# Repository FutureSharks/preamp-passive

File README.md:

# Preamp - Passive

This is the Arduino code, PCB layouts and 3D drawings for a HiFi passive preamplifier. It has the following features:

  * Volume control and input selection via encoder and Apple remote.
  * Uses a 256 step R2R relayed based attenuator.
  * Completely passive.
  * Only 5V power required.
  * [Adafruit NeoPixel](http://www.adafruit.com/category/168) shows volume level with colour.
  * Sleep mode with low power consumption: 0.9W.

Full build details can be found here:
http://www.diyaudio.com/forums/analog-line-level/275446-passive-preamp-arduino-based-remote-control-relay-r2r-input-selection.html

## Hardware

  * [MCP23S17](http://www.microchip.com/wwwproducts/Devices.aspx?product=MCP23S17): Controlled via SPI. This is the R2R relayed attenuator and controls the volume.
  * [MCP23S08](http://www.microchip.com/wwwproducts/Devices.aspx?product=MCP23S08): Controlled via SPI. For the input selector and mute.
  * [Adafruit NeoPixel](http://www.adafruit.com/category/168): Controlled via a single-wire control protocol.
  * IR sensor: Standard 38Khz type.
  * [Bourns EM14](https://www.bourns.com/pdfs/em14.pdf) Rotary Optical Encoder with switch.
  * [Modushop Galaxy Maggiorato GX187](http://www.modu.it/galaxyeng.html) with custom machined front and rear.

PCB and schematics are provided in EAGLE PCB format.

Front and rear panel 3D drawings are in AutoCAD format.

The IRremote library is from here:
https://github.com/z3t0/Arduino-IRremote

Adafruit NeoPixel library is from here:
https://github.com/adafruit/Adafruit_NeoPixel

## Photos

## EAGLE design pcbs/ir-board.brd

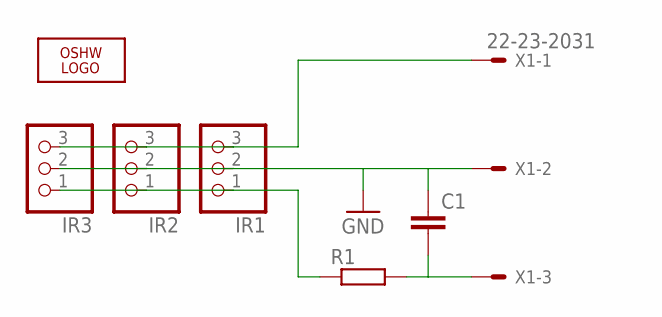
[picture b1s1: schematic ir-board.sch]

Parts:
C1: C-EUC1206; C1206
IR1, IR2, IR3: PINHD-1X3; 1X03
LOGO1: OSHW_LOGO_6MILX0200-NT; OSHW_6X200_NOTEXT
R1: R-EU_R1206; R1206
X1: 22-23-2031

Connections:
GND: C1.1, IR1.2, IR2.2, IR3.2, X1.2
unnamed: C1.2, R1.2, X1.3
OUT: IR1.3, IR2.3, IR3.3, X1.1
VS: IR1.1, IR2.1, IR3.1, R1.1

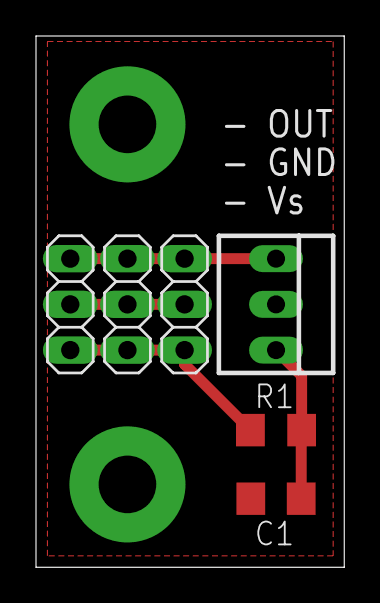
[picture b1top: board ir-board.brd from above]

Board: 2 copper layers, 17.1 x 29.5 mm, 7 parts (1 on the bottom side), 4 nets.

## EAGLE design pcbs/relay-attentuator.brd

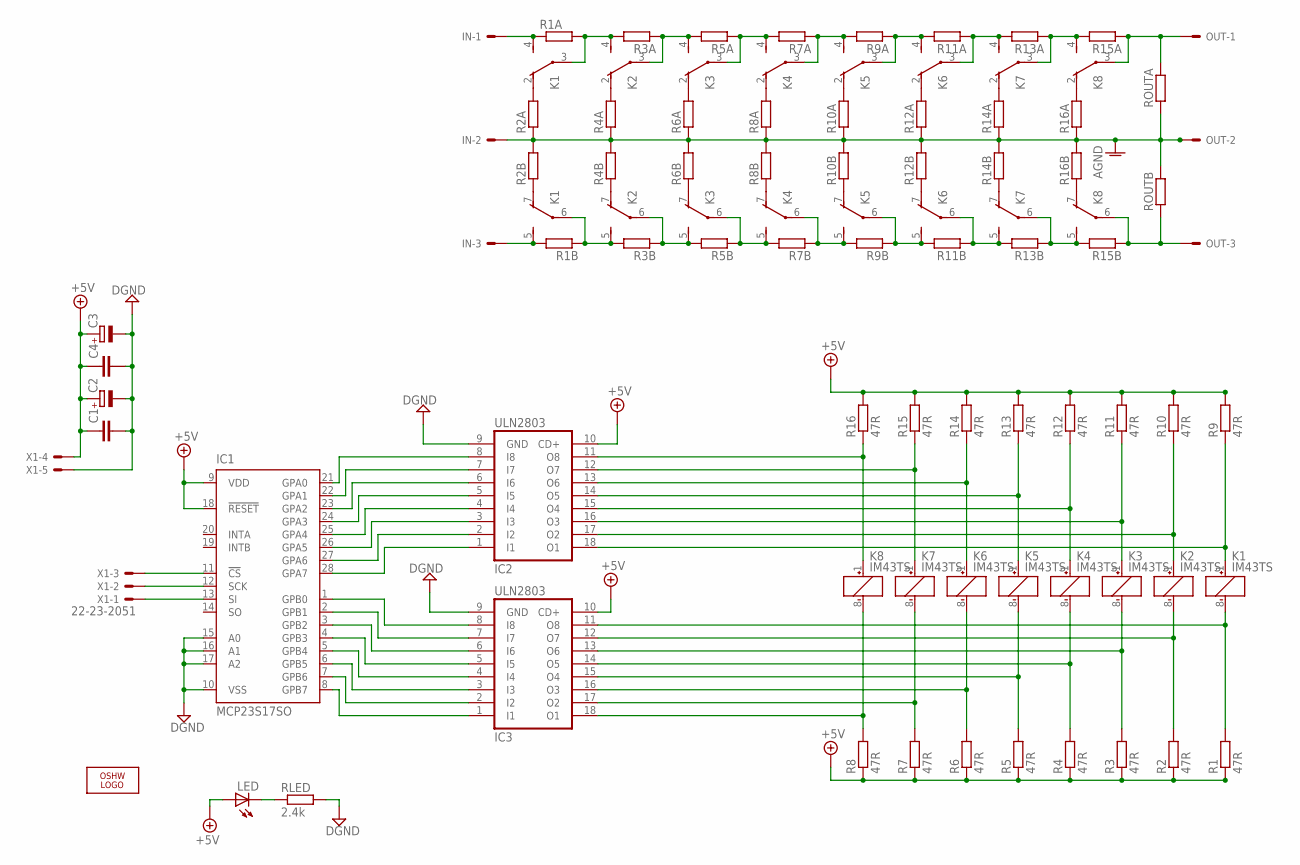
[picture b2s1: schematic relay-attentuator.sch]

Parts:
C1, C4: C-EUC1206; C1206
C2, C3: CPOL-EUE3.5-8; E3,5-8
IC1: MCP23S17SO; SO28W
IC2, IC3: ULN2803; SO-18W
IN: 22-23-2031
K1, K2, K3, K4, K5, K6, K7, K8: IM43TS
LED: LEDCHIPLED_1206; CHIPLED_1206
LOGO1: OSHW_LOGO_FILLX0200-NT; OSHW_FILLX200_NOTEXT
OUT: 22-23-2031
R1, R2, R3, R4, R5, R6, R7, R8, R9, R10, R11, R12, R13, R14, R15, R16: 47R; R1206
R1A, R1B, R2A, R2B, R3A, R3B, R4A, R4B, R5A, R5B, R6A, R6B, R7A, R7B, R8A, R8B, R9A, R9B, R10A, R10B, R11A, R11B, R12A, R12B, R13A, R13B, R14A, R14B, R15A, R15B, R16A, R16B: R-EU_R1206; R1206
RLED: 2.4k; R1206
ROUTA: R-EU_R1206; R1206
ROUTB: R-EU_R1206; R1206
X1: 22-23-2051

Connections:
+5V: C1.1, C2.+, C3.+, C4.1, IC1.9 (VDD), IC1.18 (!RESET), IC2.10 (CD+), IC3.10 (CD+), LED.A, R1.1, R2.1, R3.1, R4.1, R5.1, R6.1, R7.1, R8.1, R9.2, R10.2, R11.2, R12.2, R13.2, R14.2, R15.2, R16.2, X1.4
AGND: IN.2, OUT.2, R2A.1, R2B.2, R4A.1, R4B.2, R6A.1, R6B.2, R8A.1, R8B.2, R10A.1, R10B.2, R12A.1, R12B.2, R14A.1, R14B.2, R16A.1, R16B.2, ROUTA.1, ROUTB.2
ATT_INL: IN.1, K1.4 (S), R1A.1
ATT_INR: IN.3, K1.5 (S), R1B.2
CS: IC1.11 (!CS), X1.3
DGND: C1.2, C2.-, C3.-, C4.2, IC1.10 (VSS), IC1.15 (A0), IC1.16 (A1), IC1.17 (A2), IC2.9 (GND), IC3.9 (GND), RLED.2, X1.5
unnamed: IC2.11 (O8), K8.1 (+), R16.1
unnamed: IC3.11 (O8), K1.8 (-), R1.2
unnamed: IC3.17 (O2), K7.8 (-), R7.2
unnamed: IC3.13 (O6), K3.8 (-), R3.2
unnamed: IC3.14 (O5), K4.8 (-), R4.2
unnamed: K2.7 (O), R4B.1
unnamed: K1.7 (O), R2B.1
unnamed: K1.2 (O), R2A.2
unnamed: IC3.18 (O1), K8.8 (-), R8.2
unnamed: IC2.12 (O7), K7.1 (+), R15.1
unnamed: IC2.13 (O6), K6.1 (+), R14.1
unnamed: IC2.14 (O5), K5.1 (+), R13.1
unnamed: IC2.15 (O4), K4.1 (+), R12.1
unnamed: IC2.16 (O3), K3.1 (+), R11.1
unnamed: IC2.17 (O2), K2.1 (+), R10.1
unnamed: IC2.18 (O1), K1.1 (+), R9.1
unnamed: K3.7 (O), R6B.1
unnamed: IC3.12 (O7), K2.8 (-), R2.2
unnamed: IC3.16 (O3), K6.8 (-), R6.2
unnamed: IC3.15 (O4), K5.8 (-), R5.2
unnamed: K4.7 (O), R8B.1
unnamed: K5.7 (O), R10B.1
unnamed: K6.7 (O), R12B.1
unnamed: K7.7 (O), R14B.1
unnamed: K8.7 (O), R16B.1
unnamed: K2.2 (O), R4A.2
unnamed: K3.2 (O), R6A.2
unnamed: K4.2 (O), R8A.2
unnamed: K5.2 (O), R10A.2
unnamed: K6.2 (O), R12A.2
unnamed: K7.2 (O), R14A.2
unnamed: K8.2 (O), R16A.2
unnamed: IC1.28 (GPA7), IC2.1 (I1)
unnamed: IC1.27 (GPA6), IC2.2 (I2)
unnamed: IC1.26 (GPA5), IC2.3 (I3)
unnamed: IC1.25 (GPA4), IC2.4 (I4)
unnamed: IC1.24 (GPA3), IC2.5 (I5)
unnamed: IC1.23 (GPA2), IC2.6 (I6)
unnamed: IC1.22 (GPA1), IC2.7 (I7)
unnamed: IC1.21 (GPA0), IC2.8 (I8)
unnamed: IC1.8 (GPB7), IC3.1 (I1)
unnamed: IC1.7 (GPB6), IC3.2 (I2)
unnamed: IC1.6 (GPB5), IC3.3 (I3)
unnamed: IC1.5 (GPB4), IC3.4 (I4)
unnamed: IC1.4 (GPB3), IC3.5 (I5)
unnamed: IC1.3 (GPB2), IC3.6 (I6)
unnamed: IC1.2 (GPB1), IC3.7 (I7)
unnamed: IC1.1 (GPB0), IC3.8 (I8)
unnamed: K7.6, K8.5 (S), R13B.1, R15B.2
unnamed: K7.3, K8.4 (S), R13A.1, R15A.2
unnamed: K6.6, K7.5 (S), R11B.1, R13B.2
unnamed: LED.C, RLED.1
unnamed: K8.6, OUT.3, R15B.1, ROUTB.1
unnamed: K8.3, OUT.1, R15A.1, ROUTA.2
unnamed: K1.3, K2.4 (S), R1A.2, R3A.2
unnamed: K2.3, K3.4 (S), R3A.1, R5A.2
unnamed: K1.6, K2.5 (S), R1B.1, R3B.2
unnamed: K3.3, K4.4 (S), R5A.1, R7A.2
unnamed: K4.3, K5.4 (S), R7A.1, R9A.2
unnamed: K5.3, K6.4 (S), R9A.1, R11A.2
unnamed: K6.3, K7.4 (S), R11A.1, R13A.2
unnamed: K2.6, K3.5 (S), R3B.1, R5B.2
unnamed: K3.6, K4.5 (S), R5B.1, R7B.2
unnamed: K4.6, K5.5 (S), R7B.1, R9B.2
unnamed: K5.6, K6.5 (S), R9B.1, R11B.2
SCK: IC1.12 (SCK), X1.2
SI: IC1.13 (SI), X1.1

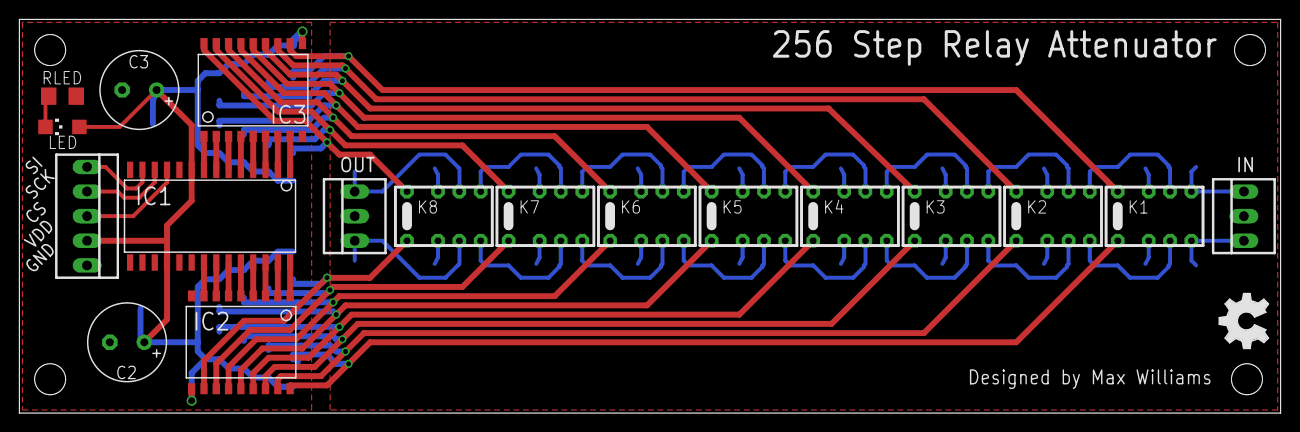
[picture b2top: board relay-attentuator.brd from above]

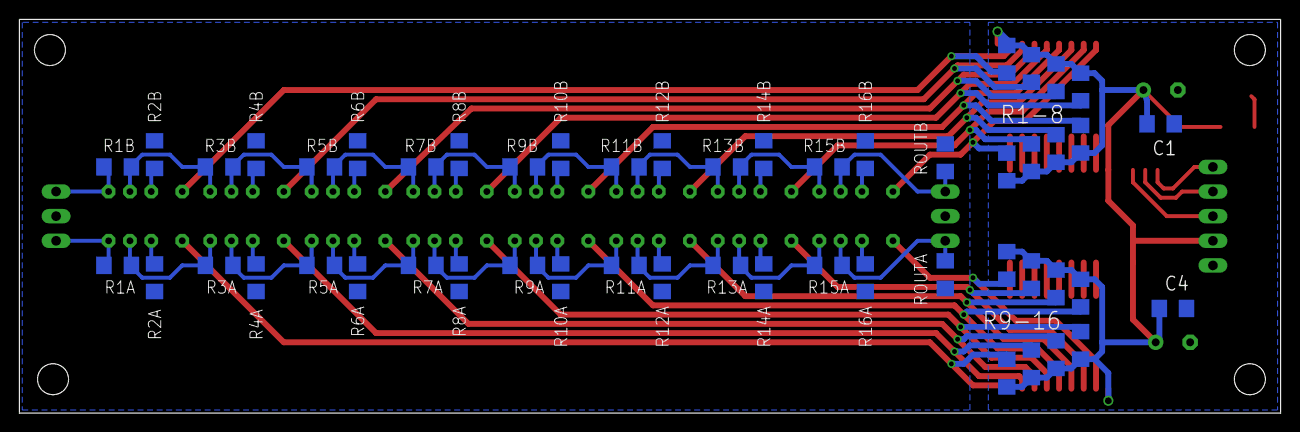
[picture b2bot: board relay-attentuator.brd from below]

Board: 2 copper layers, 130.2 x 40.6 mm, 71 parts (52 on the bottom side), 73 nets.

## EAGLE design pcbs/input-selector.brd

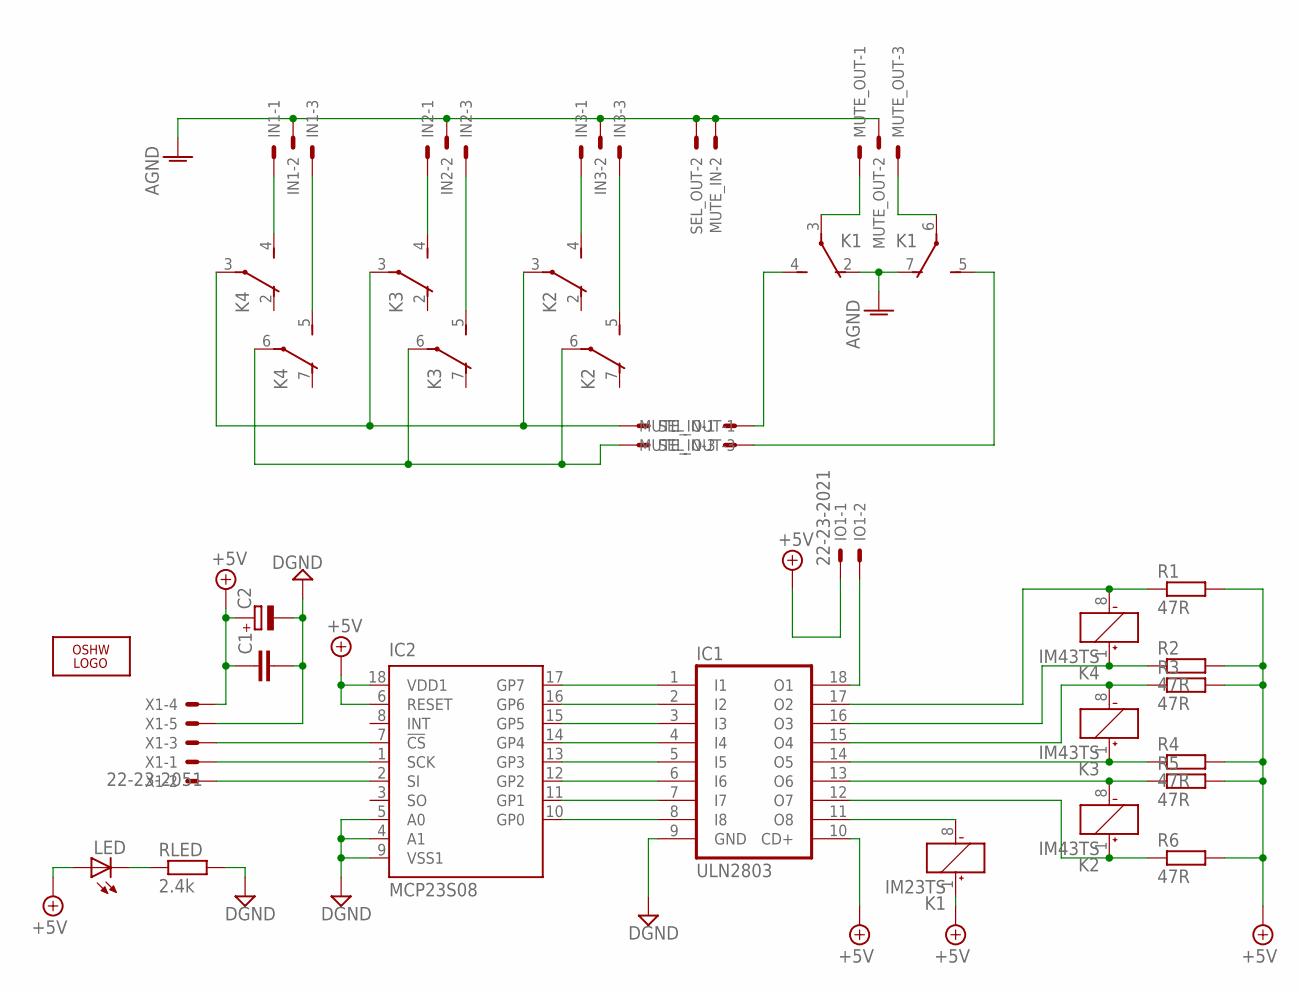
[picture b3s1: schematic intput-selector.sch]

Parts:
C1: C-EUC1206; C1206
C2: CPOL-EUC; PANASONIC_C
IC1: ULN2803; SO-18W
IC2: MCP23S08; SO-18W
IN1, IN2, IN3: 22-23-2031
IO1: 22-23-2021
K1: IM23TS; IM43TS
K2, K3, K4: IM43TS
LED: LEDCHIPLED_1206; CHIPLED_1206
LOGO1: OSHW_LOGO_FILLX0200-NT; OSHW_FILLX200_NOTEXT
MUTE_IN: 22-23-2031
MUTE_OUT: 22-23-2031
R1, R2, R3, R4, R5, R6: 47R; R1206
RLED: 2.4k; R1206
SEL_OUT: 22-23-2031
X1: 22-23-2051

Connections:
+5V: C1.1, C2.+, IC1.10 (CD+), IC2.6 (RESET), IC2.18 (VDD1), IO1.1, K1.1 (+), LED.A, R1.2, R2.2, R3.2, R4.2, R5.2, R6.2, X1.4
AGND: IN1.2, IN2.2, IN3.2, K1.2 (O), K1.7 (O), MUTE_IN.2, MUTE_OUT.2, SEL_OUT.2
CS: IC2.7 (!CS), X1.3
DGND: C1.2, C2.-, IC1.9 (GND), IC2.4 (A1), IC2.5 (A0), IC2.9 (VSS1), RLED.2, X1.5
INL: K2.3, K3.3, K4.3, SEL_OUT.1
INR: K2.6, K3.6, K4.6, SEL_OUT.3
unnamed: IC1.1 (I1), IC2.17 (GP7)
unnamed: IC1.2 (I2), IC2.16 (GP6)
unnamed: IC1.3 (I3), IC2.15 (GP5)
unnamed: IC1.5 (I5), IC2.13 (GP3)
unnamed: IC1.6 (I6), IC2.12 (GP2)
unnamed: IC1.7 (I7), IC2.11 (GP1)
unnamed: IC1.4 (I4), IC2.14 (GP4)
unnamed: IC1.8 (I8), IC2.10 (GP0)
unnamed: IC1.16 (O3), K4.1 (+), R2.1
unnamed: IC1.14 (O5), K3.1 (+), R4.1
unnamed: IC1.13 (O6), K2.8 (-), R5.1
unnamed: IC1.12 (O7), K2.1 (+), R6.1
unnamed: IC1.15 (O4), K3.8 (-), R3.1
unnamed: IC1.11 (O8), K1.8 (-)
unnamed: IC1.17 (O2), K4.8 (-), R1.1
unnamed: IC1.18 (O1), IO1.2
unnamed: K1.6, MUTE_OUT.3
unnamed: K1.3, MUTE_OUT.1
unnamed: IN1.1, K4.4 (S)
unnamed: IN1.3, K4.5 (S)
unnamed: IN2.1, K3.4 (S)
unnamed: IN2.3, K3.5 (S)
unnamed: IN3.1, K2.4 (S)
unnamed: IN3.3, K2.5 (S)
unnamed: LED.C, RLED.1
OUTL: K1.4 (S), MUTE_IN.1
OUTR: K1.5 (S), MUTE_IN.3
SCK: IC2.1 (SCK), X1.1
SI: IC2.2 (SI), X1.2

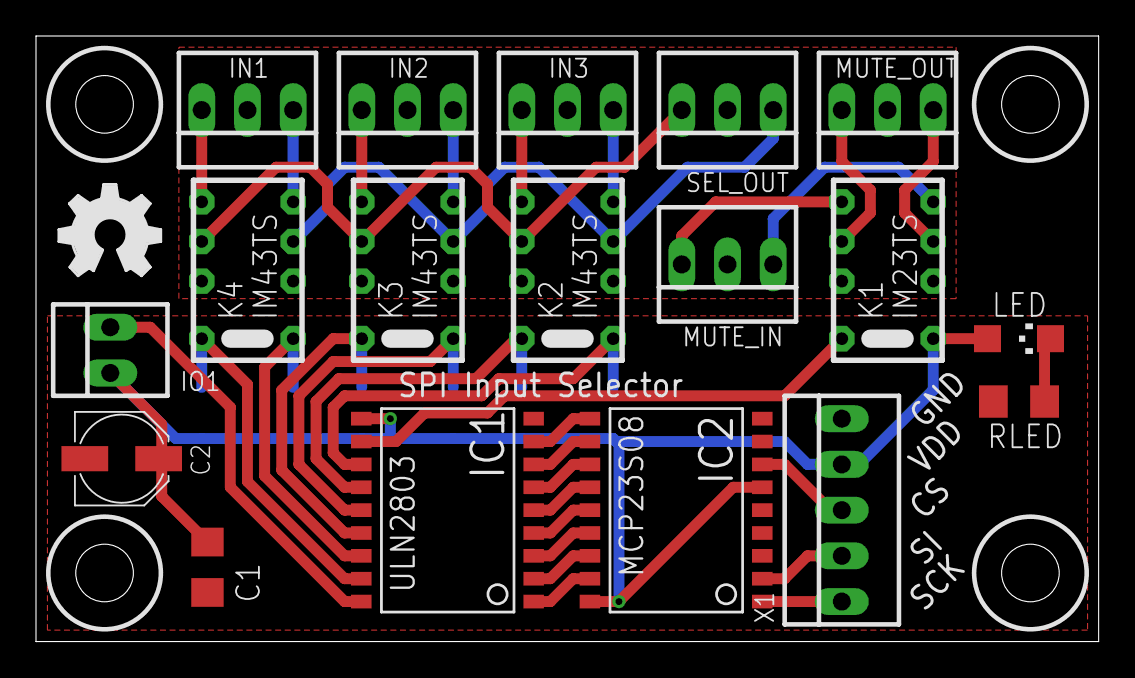
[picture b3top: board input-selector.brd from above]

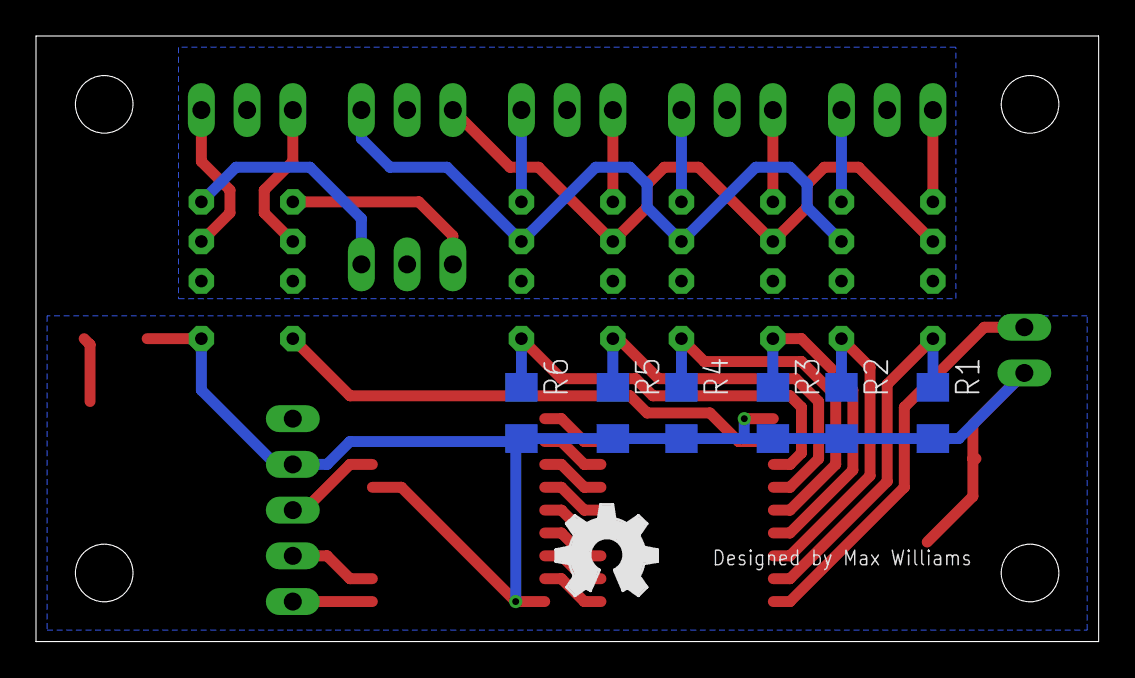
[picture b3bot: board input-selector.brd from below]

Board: 2 copper layers, 59.0 x 33.6 mm, 26 parts (7 on the bottom side), 35 nets.

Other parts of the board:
LOGO2: OSHW_LOGO_FILLX0200-NT; OSHW_FILLX200_NOTEXT

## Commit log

2015-08-30 Initial commit.
2015-08-30 Adding two libraries
2015-08-30 Adding images and readme.
2015-08-30 Fixing readme title.
2015-11-02 Removing bad debug serial.print statements.
2015-11-04 These are remote codes for the other version alu remote.
2015-11-14 Adding license, more photos and PCB files.
2015-11-14 Small update to readme
2015-11-14 Adding links to readme and add 3D drawings too.
2016-10-03 Adding BoM file
2016-10-03 Update preamp-passive.ino
    Making IR pins consistent with diagram
2016-10-03 Updating connection diagram
2016-10-03 Updating images
